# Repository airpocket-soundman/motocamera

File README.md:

# motocamera
The project to digitize Pathé's MotoCamera.

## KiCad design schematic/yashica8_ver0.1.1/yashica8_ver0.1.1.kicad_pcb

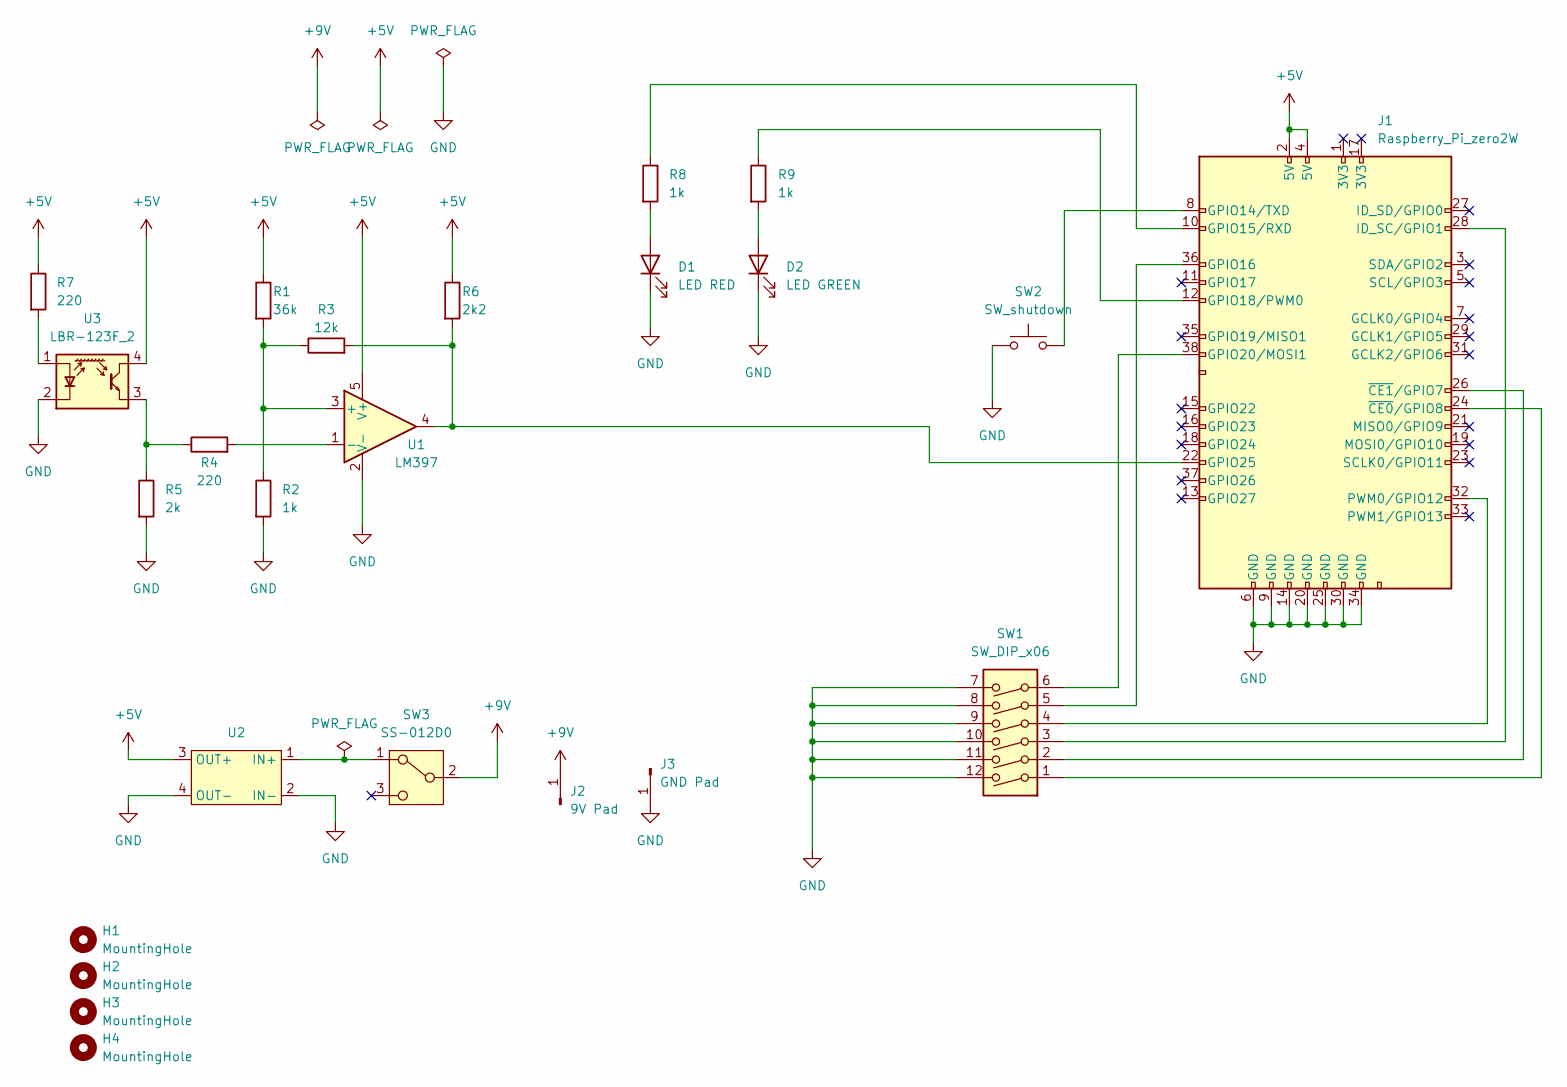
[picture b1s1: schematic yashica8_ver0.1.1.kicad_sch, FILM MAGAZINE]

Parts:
D1: LED RED; LED_D3.0mm
D2: LED GREEN; LED_D3.0mm
H1, H2, H3, H4: MountingHole; MountingHole_2.1mm
J1: Raspberry_Pi_zero2W; raspberry Pi socket 2x19
J2: 9V Pad; SolderWirePad_1x01_SMD_1x2mm
J3: GND Pad; SolderWirePad_1x01_SMD_1x2mm
R1: 36k; R_0805_2012Metric_Pad1.20x1.40mm_HandSolder
R2, R8, R9: 1k; R_0805_2012Metric_Pad1.20x1.40mm_HandSolder
R3: 12k; R_0805_2012Metric_Pad1.20x1.40mm_HandSolder
R4, R7: 220; R_0805_2012Metric_Pad1.20x1.40mm_HandSolder
R5: 2k; R_0805_2012Metric_Pad1.20x1.40mm_HandSolder
R6: 2k2; R_0805_2012Metric_Pad1.20x1.40mm_HandSolder
SW1: SW_DIP_x06; SW_DIP_SPSTx06_Slide_9.78x17.42mm_W7.62mm_P2.54mm
SW2: SW_shutdown; SW_PUSH_6mm
SW3: SS-012D0; slide_switch
U1: LM397; SOT-23-5
U2: MP2307 DC-DC Board
U3: LBR-123F_2

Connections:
+5V: J1.2 (5V), J1.4 (5V), R1.1, R6.1, R7.1, U1.5 (V+), U2.3 (OUT+), U3.4
+9V: J2.1, SW3.2
GND: D1.1 (K), D2.1 (K), J1.6 (GND), J1.9 (GND), J1.14 (GND), J1.20 (GND), J1.25 (GND), J1.30 (GND), J1.34 (GND), J3.1, R2.2, R5.2, SW1.7, SW1.8, SW1.9, SW1.10, SW1.11, SW1.12, SW2.1, U1.2 (V-), U2.2 (IN-), U2.4 (OUT-), U3.2 (K)
unnamed: D1.2 (A), R8.2
unnamed: D2.2 (A), R9.2
unnamed: J1.8 (GPIO14/TXD), SW2.2
unnamed: J1.10 (GPIO15/RXD), R8.1
unnamed: J1.36 (GPIO16), SW1.5
unnamed: J1.12 (GPIO18/PWM0), R9.1
unnamed: J1.38 (GPIO20/MOSI1), SW1.6
unnamed: J1.22 (GPIO25), R3.2, R6.2, U1.4
unnamed: J1.28 (ID_SC/GPIO1), SW1.3
unnamed: J1.32 (PWM0/GPIO12), SW1.4
unnamed: J1.24 (~CE0/GPIO8), SW1.1
unnamed: J1.26 (~CE1/GPIO7), SW1.2
unnamed: R4.1, R5.1, U3.3
unnamed: R1.2, R2.1, R3.1, U1.3 (+)
unnamed: R4.2, U1.1 (-)
unnamed: SW3.1, U2.1 (IN+)
unnamed: R7.2, U3.1 (A)

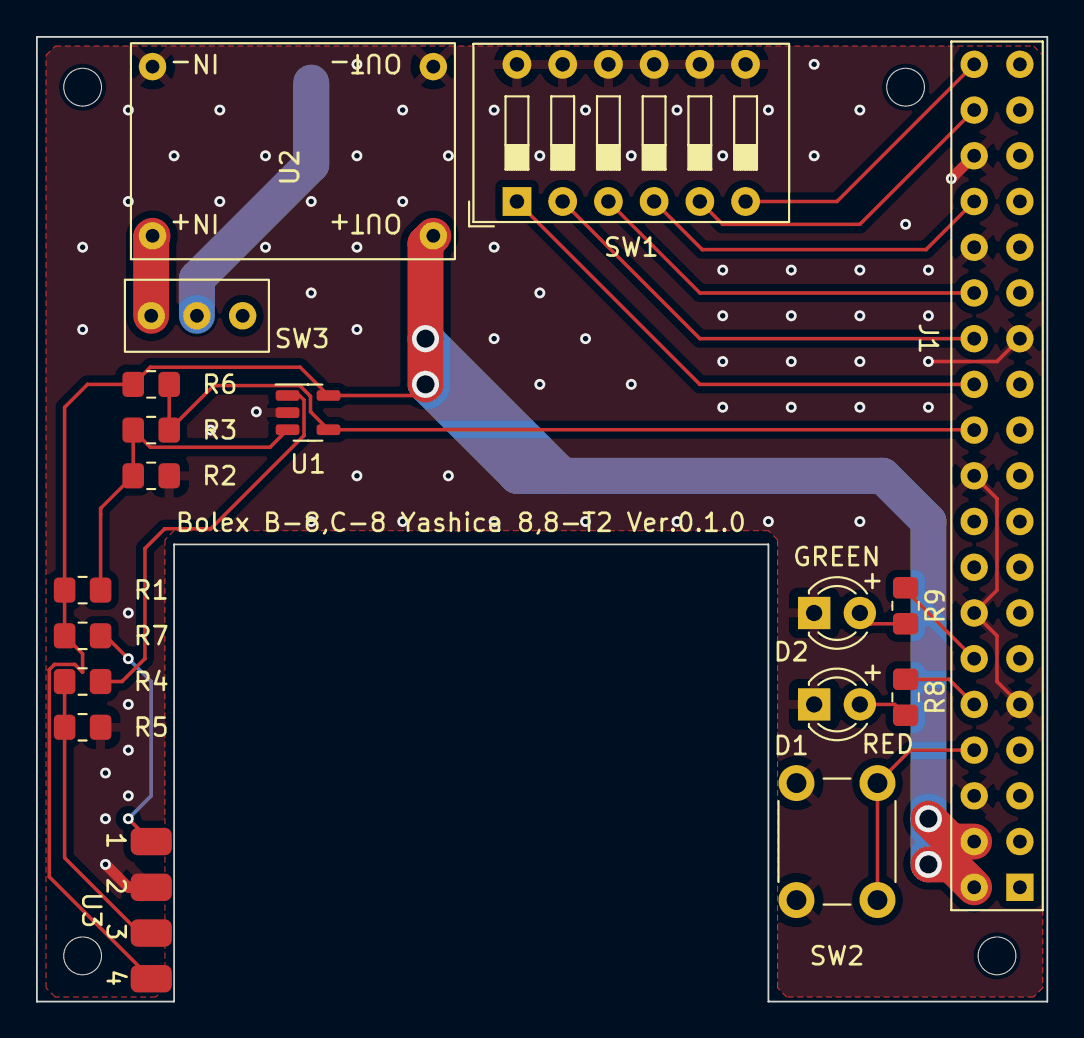
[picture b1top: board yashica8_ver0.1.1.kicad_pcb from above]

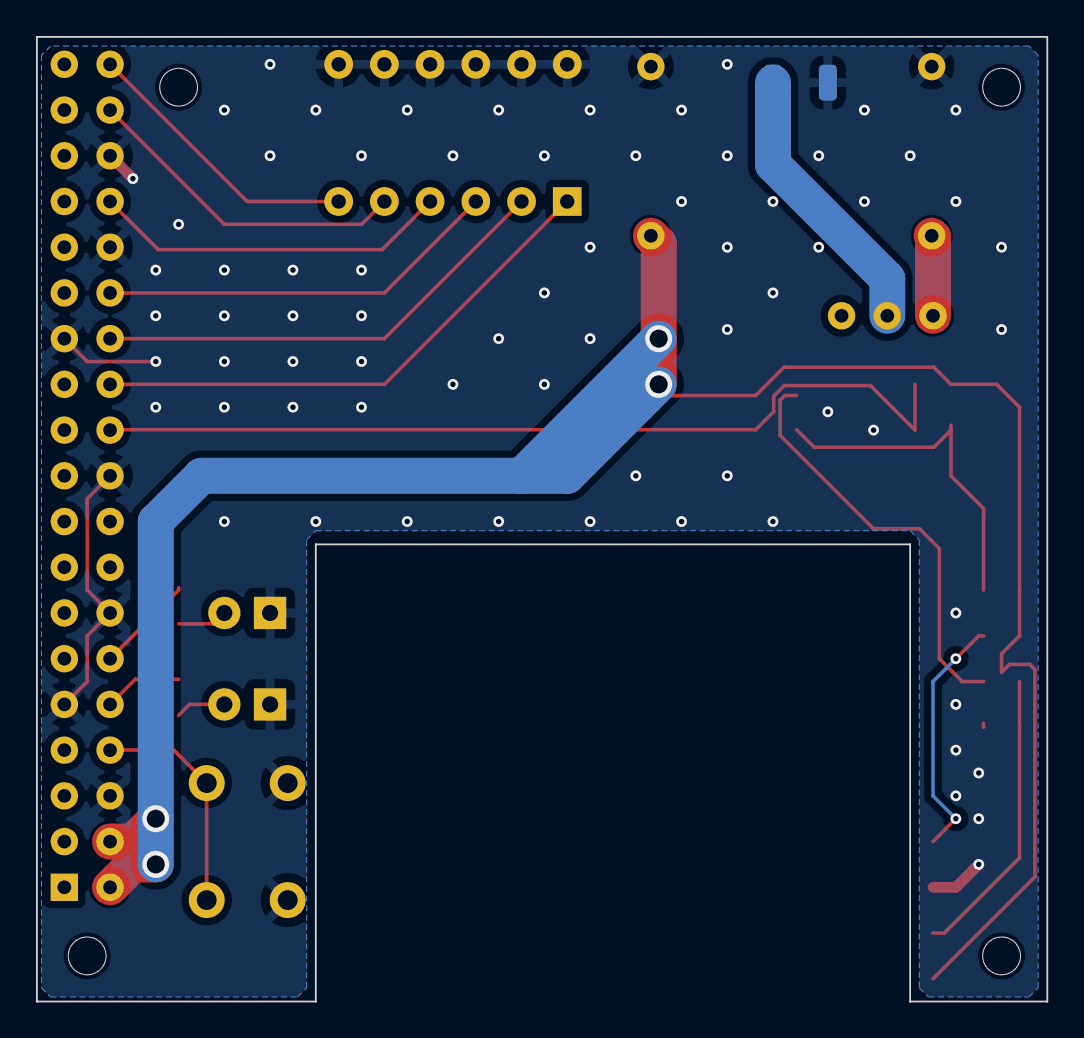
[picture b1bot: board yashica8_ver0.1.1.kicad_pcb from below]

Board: 2 copper layers, 56.1 x 53.6 mm, 24 parts (2 on the bottom side), 20 nets.

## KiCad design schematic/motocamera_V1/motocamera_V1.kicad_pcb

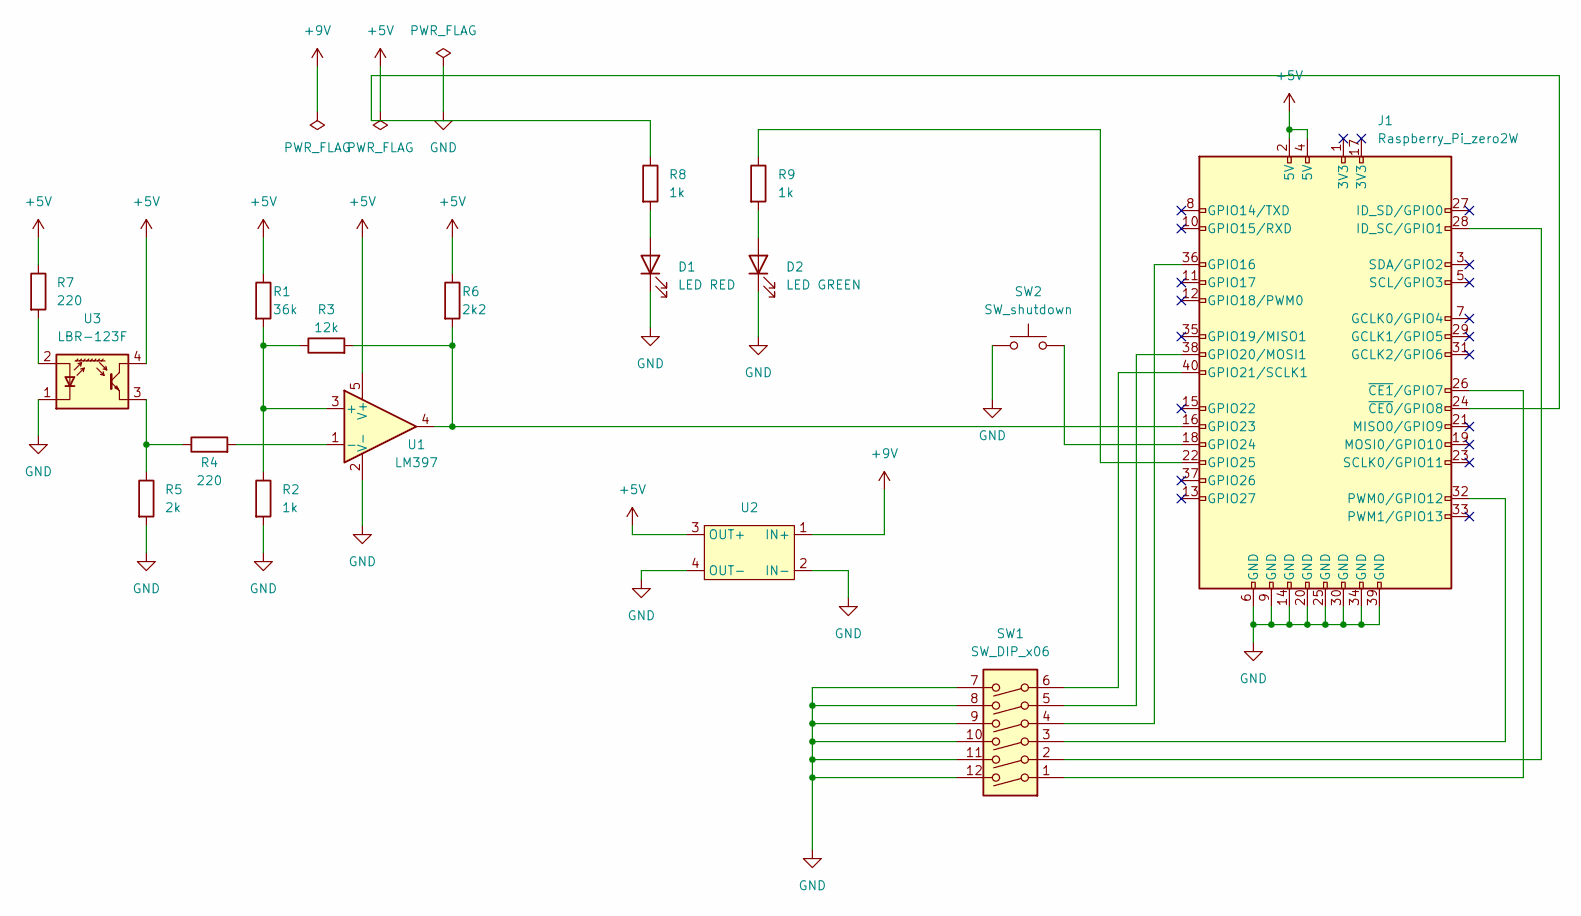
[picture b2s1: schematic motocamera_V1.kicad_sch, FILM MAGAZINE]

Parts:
D1: LED RED; LED_D3.0mm
D2: LED GREEN; LED_D3.0mm
J1: Raspberry_Pi_zero2W; PinHeader_2x20_P2.54mm_Vertical
R1: 36k; R_0805_2012Metric_Pad1.20x1.40mm_HandSolder
R2, R8, R9: 1k; R_0805_2012Metric_Pad1.20x1.40mm_HandSolder
R3: 12k; R_0805_2012Metric_Pad1.20x1.40mm_HandSolder
R4, R7: 220; R_0805_2012Metric_Pad1.20x1.40mm_HandSolder
R5: 2k; R_0805_2012Metric_Pad1.20x1.40mm_HandSolder
R6: 2k2; R_0805_2012Metric_Pad1.20x1.40mm_HandSolder
SW1: SW_DIP_x06; SW_DIP_SPSTx06_Slide_9.78x17.42mm_W7.62mm_P2.54mm
SW2: SW_shutdown; SW_PUSH_6mm
U1: LM397; SOT-23-5
U2: MP2307 DC-DC Board
U3: LBR-123F

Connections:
+5V: J1.2 (5V), J1.4 (5V), R1.1, R6.1, R7.1, U1.5 (V+), U2.3 (OUT+), U3.4
+9V: U2.1 (IN+)
GND: D1.1 (K), D2.1 (K), J1.6 (GND), J1.9 (GND), J1.14 (GND), J1.20 (GND), J1.25 (GND), J1.30 (GND), J1.34 (GND), J1.39 (GND), R2.2, R5.2, SW1.7, SW1.8, SW1.9, SW1.10, SW1.11, SW1.12, SW2.1, U1.2 (V-), U2.2 (IN-), U2.4 (OUT-), U3.1 (K)
unnamed: D1.2 (A), R8.2
unnamed: D2.2 (A), R9.2
unnamed: J1.36 (GPIO16), SW1.4
unnamed: J1.38 (GPIO20/MOSI1), SW1.5
unnamed: J1.40 (GPIO21/SCLK1), SW1.6
unnamed: J1.16 (GPIO23), R3.2, R6.2, U1.4
unnamed: J1.18 (GPIO24), SW2.2
unnamed: J1.22 (GPIO25), R9.1
unnamed: J1.28 (ID_SC/GPIO1), SW1.2
unnamed: J1.32 (PWM0/GPIO12), SW1.3
unnamed: J1.24 (~CE0/GPIO8), R8.1
unnamed: J1.26 (~CE1/GPIO7), SW1.1
unnamed: R4.1, R5.1, U3.3
unnamed: R1.2, R2.1, R3.1, U1.3 (+)
unnamed: R4.2, U1.1 (-)
unnamed: R7.2, U3.2 (A)

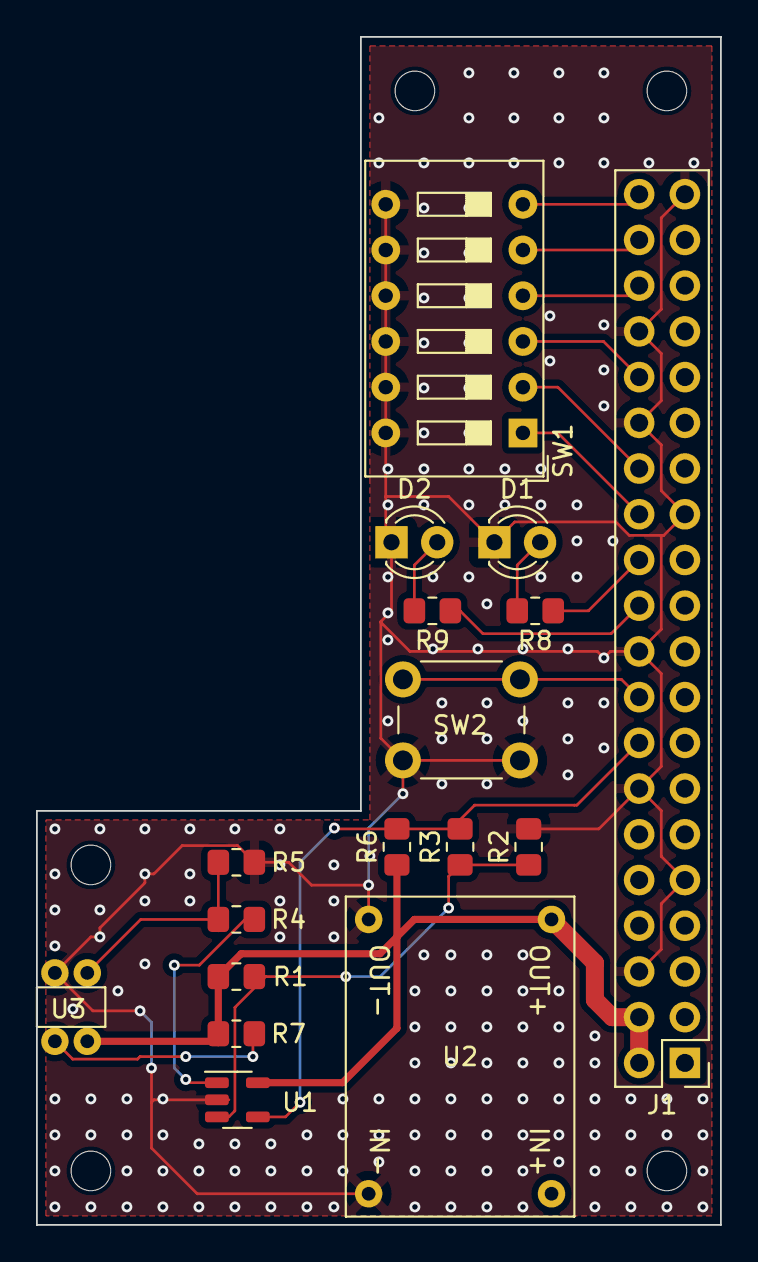
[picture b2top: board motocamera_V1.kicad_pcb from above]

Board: 2 copper layers, 38.0 x 66.0 mm, 22 parts (0 on the bottom side), 18 nets.

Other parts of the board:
MH1, MH1#2, MH1#3, MH1#4, MH1#5: MountingHole_2.2mm_M2

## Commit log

2024-02-20 change schematic
2024-02-22 readme,motocamera.py
2024-02-22 stream.py動かない
2024-02-23 test code追加
2024-03-08 test code 作った
2024-03-14 movie_rec_dev1.py
2024-03-15 timer_rec.py
2024-03-15 frame数増加
2024-03-15 test
2024-03-19 simple
2024-03-20 simple_GPIO_rec2.py を暫定fix
2024-03-20 2023.3.21 picamera2検証用
2024-03-21 frame duration limitの動的変更テスト
2024-03-21 frame_duration_limit_change_test.pyでカメラ単体でのテスト。
2024-03-21 simple_GPIO_rec2_lightweight_without_interrupt.pyで割込みなしの検証を実施
2024-03-21 simple_GPIO_rec4.py
2024-03-21 回路図修正
2024-03-21 ファイル移動 /src to /src/dev
2024-03-22 meta_data記入テスト
2024-03-22 sync関係の検討いろいろ
2024-04-17 without_shutter.py
2024-04-19 setpu.md 誤記訂正
2024-04-19 without_shutter.pyしりーずを更新
2024-04-20 without_shutter02.pyでシャッター非同期撮影をいろいろ確認
2024-04-21 md修正
2024-04-22 microSD_setup.md誤記修正
2024-04-26 md誤記修正
2024-04-26 flask
2024-05-08 yashica8用基板データ追加
2024-05-10 cinemax8基板設計
2024-05-10 誤記訂正
2024-05-10 picamera2の撮影パラメータ設定を追加
2024-05-10 先頭のフレームバッファをキャンセルするテストいろいろ
2024-05-10 video_config修正
2024-05-14 yashika/bolex基板、修正
2024-05-17 基板設計
2024-06-18 schematic
2024-06-18 yashica_ver0.1.1 schematic
2024-09-04 board 0.1.2 added
2024-09-05 Bookworm のUSB SSH設定追記
2024-10-07 Update microSD_setup.md
    add os download address
